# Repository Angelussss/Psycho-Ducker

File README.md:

# Psycho Ducker

Welcome to the Psycho Ducker, a 75% exploded keyboard project! This is a hot-swappable, compact, and efficient keyboard. Below, you'll find all the details you need to build and understand this project.

## Layout

The keyboard features a 75% exploded layout, offering a balance between functionality and compactness. The exploded design separates key clusters for a modern aesthetic and improved usability.

## Components

### Essentials

-   **MCU:** STM32F072CBT6.
    
-   **Switches:** Cherry MX style (supports both 3-pin and 5-pin switches).
    
-   **Keycaps:** Standard keycap set compatible with the Cherry MX stem.
    
-   **Diodes:** SOD-123.
    
-   **Hot-swap sockets:** Kailh are recommended.

### Optionals

-   **M2 screws** (to secure the PCB to the case or standoffs).
    
-   **M2 standoffs** (for added stability between the PCB and case).
    
-   **Stabilizers** (PCB-mounted, required for larger keys like the spacebar, enter, and shift).

## Required Tools

-   **Soldering iron**: Required for soldering pretty much the whole project.

- **heatgun**: Heavily hinted for soldering the micro. with a basic soldering iron is very hard.
    
-   **USB cable**: Required for connecting the keyboard to your computer. The PCB uses a usb type-C connector. Be sure to have at least one usable!

## Assembly Requirements

To assemble this keyboard, you'll need medium tin soldering skills, particularly for the micro.

## Notes

-   This keyboard's PCB is designed for hot-swapping switches, making possible to change the switches without de-soldering and re-soldering.
    
-   Firmware is powered by [QMK](https://qmk.fm/), a powerful and customizable open-source keyboard firmware.
    
-   This design has been tested thoroughly and functions reliably. However, as with any DIY project, minor adjustments may be needed based on your specific components.
    
-   Feel free to use this design for personal projects, but please do not edit or misuse it.
    
-in this design there are several types of cases you might wanna use. you can find the different materials and files in the "case" folder. The case is not necessary and is hands down the hardest part as it uses specific and expensive machinery, 

## Photos

-   **Finished Build:** ![fnished keyboard photo]
    
-   **Render:** ![pcb render] (https://github.com/Angelussss/Psycho-Ducker/blob/main/images/pcb_render.png)

## Contact

For any questions, feedback, or assistance, feel free to reach out via Telegram: @AngelusPSPS.

Thank you for exploring this project! Happy building and typing!

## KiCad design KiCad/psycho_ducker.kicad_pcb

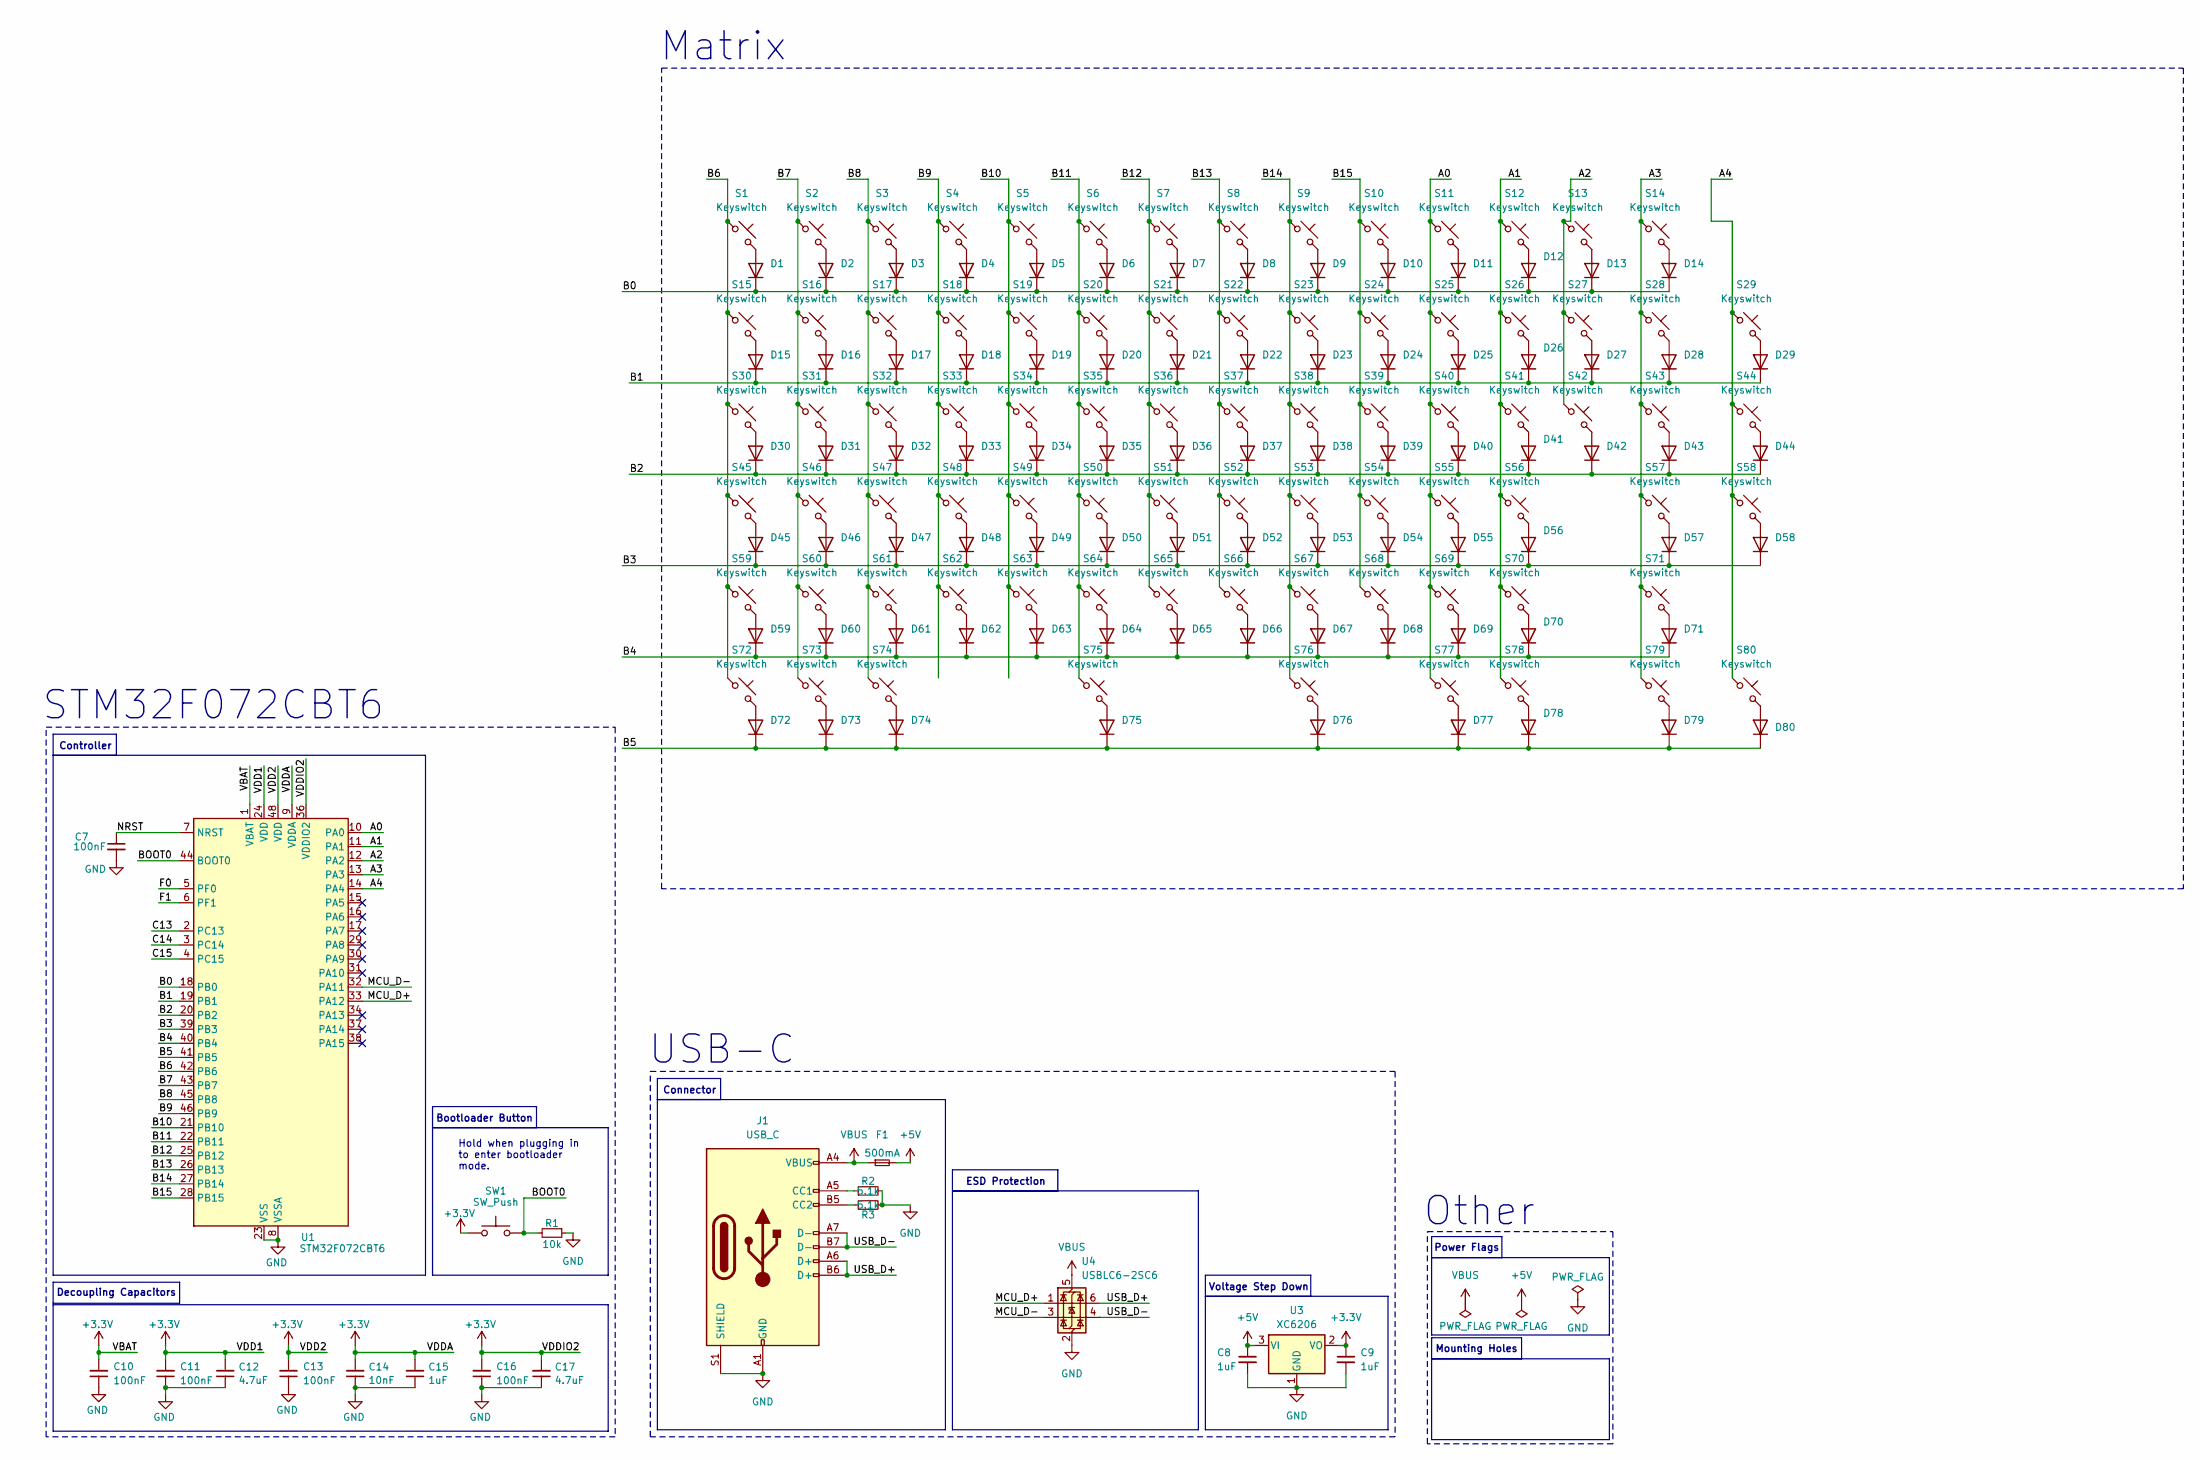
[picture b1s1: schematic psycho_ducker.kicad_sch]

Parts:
C7: 100nF; Capacitor_0402; LCSC C307331
C8, C9: 1uF; Capacitor_0402; LCSC C52923
C10, C11, C13, C16: 100nF; Capacitor_0402; MPN CL05B104KB54PNC; LCSC C307331
C12, C17: 4.7uF; Capacitor_0402; MPN CL05A475MP5NRNC; LCSC C23733
C14: 10nF; Capacitor_0402; MPN CL05B103KB5NNNC; LCSC C15195
C15: 1uF; Capacitor_0402; MPN CL05A105KA5NQNC; LCSC C52923
D1, D2, D3, D4, D5, D6, D7, D8, D9, D10, D11, D12, D13, D14, D15, D16, D17, D18, D19, D20, D21, D22, D23, D24, D25, D26, D27, D28, D29, D30, D31, D32, D33, D34, D35, D36, D37, D38, D39, D40, D41, D42, D43, D44, D45, D46, D47, D48, D49, D50, D51, D52, D53, D54, D55, D56, D57, D58, D59, D60, D61, D62, D63, D64, D65, D66, D67, D68, D69, D70, D71, D72, D73, D74, D75, D76, D77, D78, D79, D80: Diode; Diode_SOD-123
F1: 500mA; Fuse_0603; LCSC C210357
J1: USB_C; USB_C_HRO_TYPE-C-31-M-12; LCSC C165948
R1: 10k; R_0402_1005Metric; LCSC C25744
R2, R3: 5.1k; R_0402_1005Metric; LCSC C25905
S1, S2, S3, S4, S5, S6, S7, S8, S9, S10, S11, S12, S13, S14, S15, S16, S17, S18, S19, S20, S21, S22, S23, S24, S25, S26, S27, S29, S31, S32, S33, S34, S35, S36, S37, S38, S39, S40, S41, S42, S44, S46, S47, S48, S49, S50, S51, S52, S53, S54, S55, S56, S58, S60, S61, S62, S63, S64, S65, S66, S67, S68, S69, S71, S78, S79, S80: Keyswitch; Hotswap_MX_1.00u
S28: Keyswitch; Hotswap_MX_2.00u
S30, S43, S76, S77: Keyswitch; Hotswap_MX_1.50u
S45, S70: Keyswitch; Hotswap_MX_1.75u
S57, S59: Keyswitch; Hotswap_MX_2.25u
S72, S73, S74: Keyswitch; Hotswap_MX_1.25u
S75: Keyswitch; Hotswap_MX_6.25u
SW1: SW_Push; Button_TL3342; LCSC C115351
U1: STM32F072CBT6; Package_LQFP-48_7x7mm_P0.5; LCSC C81720
U3: XC6206; Voltage_SOT-23; LCSC C5446
U4: USBLC6-2SC6; ESD_SOT-23-6; LCSC C2827654

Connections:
+3.3V: C9.1, C10.2, C11.2, C12.2, C13.2, C14.2, C15.2, C16.2, C17.2, SW1.1, U1.1 (VBAT), U1.9 (VDDA), U1.24 (VDD), U1.36 (VDDIO2), U1.48 (VDD), U3.2 (VO)
+5V: C8.1, F1.2, U3.3 (VI)
/A0: S11.1, S25.1, S40.1, S55.1, S69.1, S77.1, U1.10 (PA0)
/A1: S12.1, S26.1, S41.1, S56.1, S70.1, S78.1, U1.11 (PA1)
/A2: S13.1, S27.1, S42.1, U1.12 (PA2)
/A3: S14.1, S28.1, S43.1, S57.1, S71.1, S79.1, U1.13 (PA3)
/A4: S29.1, S44.1, S58.1, S80.1, U1.14 (PA4)
/A5: U1.15 (PA5)
/A6: U1.16 (PA6)
/A7: U1.17 (PA7)
/A8: U1.29 (PA8)
/A9: U1.30 (PA9)
/A10: U1.31 (PA10)
/A13: U1.34 (PA13)
/A14: U1.37 (PA14)
/A15: U1.38 (PA15)
/B0: D1.1 (K), D2.1 (K), D3.1 (K), D4.1 (K), D5.1 (K), D6.1 (K), D7.1 (K), D8.1 (K), D9.1 (K), D10.1 (K), D11.1 (K), D12.1 (K), D13.1 (K), D14.1 (K), U1.18 (PB0)
/B1: D15.1 (K), D16.1 (K), D17.1 (K), D18.1 (K), D19.1 (K), D20.1 (K), D21.1 (K), D22.1 (K), D23.1 (K), D24.1 (K), D25.1 (K), D26.1 (K), D27.1 (K), D28.1 (K), D29.1 (K), U1.19 (PB1)
/B2: D30.1 (K), D31.1 (K), D32.1 (K), D33.1 (K), D34.1 (K), D35.1 (K), D36.1 (K), D37.1 (K), D38.1 (K), D39.1 (K), D40.1 (K), D41.1 (K), D42.1 (K), D43.1 (K), D44.1 (K), U1.20 (PB2)
/B3: D45.1 (K), D46.1 (K), D47.1 (K), D48.1 (K), D49.1 (K), D50.1 (K), D51.1 (K), D52.1 (K), D53.1 (K), D54.1 (K), D55.1 (K), D56.1 (K), D57.1 (K), D58.1 (K), U1.39 (PB3)
/B4: D59.1 (K), D60.1 (K), D61.1 (K), D62.1 (K), D63.1 (K), D64.1 (K), D65.1 (K), D66.1 (K), D67.1 (K), D68.1 (K), D69.1 (K), D70.1 (K), D71.1 (K), U1.40 (PB4)
/B5: D72.1 (K), D73.1 (K), D74.1 (K), D75.1 (K), D76.1 (K), D77.1 (K), D78.1 (K), D79.1 (K), D80.1 (K), U1.41 (PB5)
/B6: S1.1, S15.1, S30.1, S45.1, S59.1, S72.1, U1.42 (PB6)
/B7: S2.1, S16.1, S31.1, S46.1, S60.1, S73.1, U1.43 (PB7)
/B8: S3.1, S17.1, S32.1, S47.1, S61.1, S74.1, U1.45 (PB8)
/B9: S4.1, S18.1, S33.1, S48.1, S62.1, U1.46 (PB9)
/B10: S5.1, S19.1, S34.1, S49.1, S63.1, U1.21 (PB10)
/B11: S6.1, S20.1, S35.1, S50.1, S64.1, S75.1, U1.22 (PB11)
/B12: S7.1, S21.1, S36.1, S51.1, S65.1, U1.25 (PB12)
/B13: S8.1, S22.1, S37.1, S52.1, S66.1, U1.26 (PB13)
/B14: S9.1, S23.1, S38.1, S53.1, S67.1, S76.1, U1.27 (PB14)
/B15: S10.1, S24.1, S39.1, S54.1, S68.1, U1.28 (PB15)
/BOOT0: R1.2, SW1.2, U1.44 (BOOT0)
/C13: U1.2 (PC13)
/C14: U1.3 (PC14)
/C15: U1.4 (PC15)
/F0: U1.5 (PF0)
/F1: U1.6 (PF1)
/MCU_D+: U1.33 (PA12), U4.1 (I/O1)
/MCU_D-: U1.32 (PA11), U4.3 (I/O2)
/NRST: C7.1, U1.7 (NRST)
/USB_D+: J1.A6 (D+), J1.B6 (D+), U4.6 (I/O1)
/USB_D-: J1.A7 (D-), J1.B7 (D-), U4.4 (I/O2)
GND: C7.2, C8.2, C9.2, C10.1, C11.1, C12.1, C13.1, C14.1, C15.1, C16.1, C17.1, J1.A1 (GND), J1.A12 (GND), J1.B1 (GND), J1.B12 (GND), J1.S1 (SHIELD), R1.1, R2.2, R3.2, U1.8 (VSSA), U1.23 (VSS), U1.35 (VSS), U1.47 (VSS), U3.1 (GND), U4.2 (GND)
unnamed: D1.2 (A), S1.2
unnamed: D2.2 (A), S2.2
unnamed: D3.2 (A), S3.2
unnamed: D4.2 (A), S4.2
unnamed: D5.2 (A), S5.2
unnamed: D6.2 (A), S6.2
unnamed: D7.2 (A), S7.2
unnamed: D8.2 (A), S8.2
unnamed: D9.2 (A), S9.2
unnamed: D10.2 (A), S10.2
unnamed: D11.2 (A), S11.2
unnamed: D12.2 (A), S12.2
unnamed: D13.2 (A), S13.2
unnamed: D14.2 (A), S14.2
unnamed: D15.2 (A), S15.2
unnamed: D16.2 (A), S16.2
unnamed: D17.2 (A), S17.2
unnamed: D18.2 (A), S18.2
unnamed: D19.2 (A), S19.2
unnamed: D20.2 (A), S20.2
unnamed: D21.2 (A), S21.2
unnamed: D22.2 (A), S22.2
unnamed: D23.2 (A), S23.2
unnamed: D24.2 (A), S24.2
unnamed: D25.2 (A), S25.2
unnamed: D26.2 (A), S26.2
unnamed: D27.2 (A), S27.2
unnamed: D28.2 (A), S28.2
unnamed: D29.2 (A), S29.2
unnamed: D30.2 (A), S30.2
unnamed: D31.2 (A), S31.2
unnamed: D32.2 (A), S32.2
unnamed: D33.2 (A), S33.2
unnamed: D34.2 (A), S34.2
unnamed: D35.2 (A), S35.2
unnamed: D36.2 (A), S36.2
unnamed: D37.2 (A), S37.2
unnamed: D38.2 (A), S38.2
unnamed: D39.2 (A), S39.2
unnamed: D40.2 (A), S40.2
unnamed: D41.2 (A), S41.2
unnamed: D42.2 (A), S42.2
unnamed: D43.2 (A), S43.2
unnamed: D44.2 (A), S44.2
unnamed: D45.2 (A), S45.2
unnamed: D46.2 (A), S46.2
unnamed: D47.2 (A), S47.2
unnamed: D48.2 (A), S48.2
unnamed: D49.2 (A), S49.2
unnamed: D50.2 (A), S50.2
unnamed: D51.2 (A), S51.2
unnamed: D52.2 (A), S52.2
unnamed: D53.2 (A), S53.2
unnamed: D54.2 (A), S54.2
unnamed: D55.2 (A), S55.2
unnamed: D56.2 (A), S56.2
unnamed: D57.2 (A), S57.2
unnamed: D58.2 (A), S58.2
unnamed: D59.2 (A), S59.2
unnamed: D60.2 (A), S60.2
unnamed: D61.2 (A), S61.2
unnamed: D62.2 (A), S62.2
unnamed: D63.2 (A), S63.2
unnamed: D64.2 (A), S64.2
unnamed: D65.2 (A), S65.2
unnamed: D66.2 (A), S66.2
unnamed: D67.2 (A), S67.2
unnamed: D68.2 (A), S68.2
unnamed: D69.2 (A), S69.2
unnamed: D70.2 (A), S70.2
unnamed: D71.2 (A), S71.2
unnamed: D72.2 (A), S72.2
unnamed: D73.2 (A), S73.2
unnamed: D74.2 (A), S74.2
unnamed: D75.2 (A), S75.2
unnamed: D76.2 (A), S76.2
unnamed: D77.2 (A), S77.2
unnamed: D78.2 (A), S78.2
unnamed: D79.2 (A), S79.2
unnamed: D80.2 (A), S80.2
unnamed: J1.A5 (CC1), R2.1
unnamed: J1.B5 (CC2), R3.1
VBUS: F1.1, J1.A4 (VBUS), J1.A9 (VBUS), J1.B4 (VBUS), J1.B9 (VBUS), U4.5 (VBUS)

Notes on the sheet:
Hold when plugging in to enter bootloader mode.
STM32F072CBT6
USB-C
Mounting Holes
Decoupling Capacitors
Controller
ESD Protection
Power Flags
Voltage Step Down
Other
Bootloader Button
Matrix
Connector

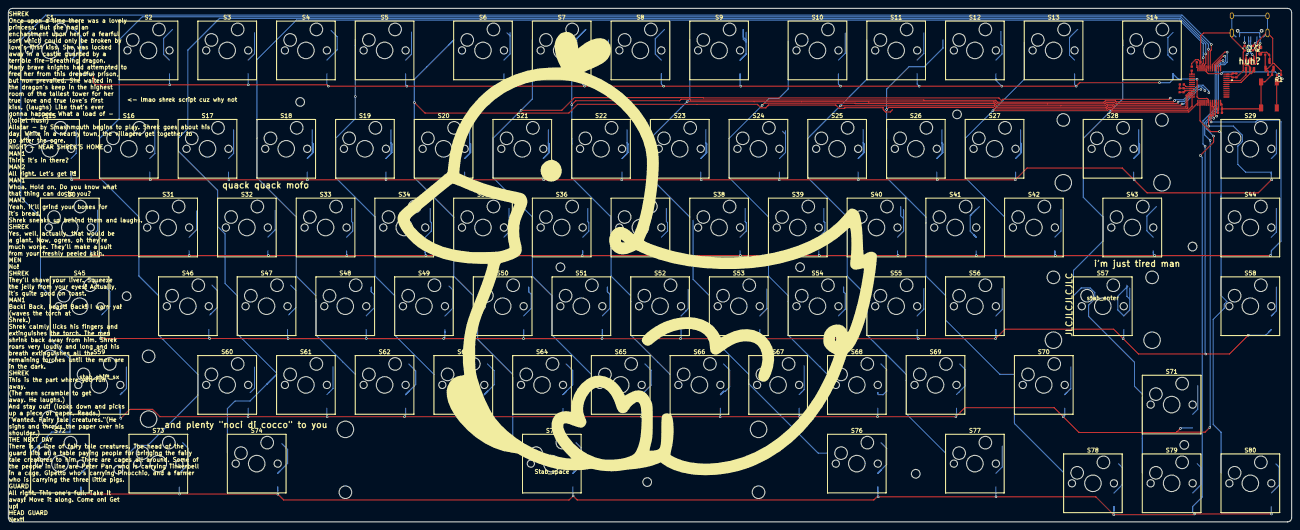
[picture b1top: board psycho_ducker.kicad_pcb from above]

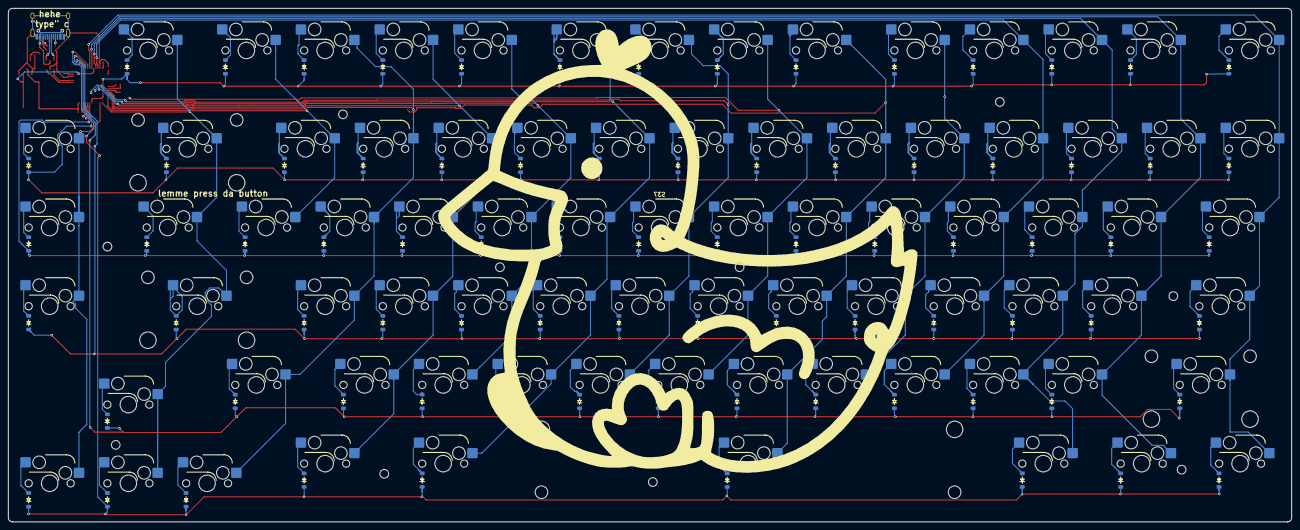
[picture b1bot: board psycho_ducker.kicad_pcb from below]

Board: 2 copper layers, 310.6 x 124.3 mm, 186 parts (82 on the bottom side), 113 nets.

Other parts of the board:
Stab_space: Stabilizer_MX_6.25u
backduck: LOGO
frontduck: LOGO
stab_backspace: Stabilizer_MX_2.00u
stab_enter: Stabilizer_MX_2.00u
stab_shift_sx: Stabilizer_MX_2.00u

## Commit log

2024-12-16 added layout from KLE
2024-12-16 edited README
2025-02-24 added v1.0.0 gerber files
2025-03-21 feat: added pcb render
2025-03-21 feat: added keyboard cads
2025-03-21 feat: added JLC order number code into f_silkscreen
2025-03-21 feat: updated production folder
2025-04-11 feat: added interactive bom
2025-04-11 feat: added pdf plot
2025-04-11 fix: c7 footprint, jlc code repetition, shrek typo and added duck
2025-04-11 feat: added micro orientation reference
2025-05-13 feat: added firmware.bin
2025-08-13 feat: added layout.json
2025-08-13 feat: started pcb front plate case
2025-08-14 fix: removed useless files
2025-08-14 feat: added front plate dxf base file
2025-08-15 feat: added front plate pcb
2025-08-15 feat: added backplate
2025-08-15 fix: useless files
2025-08-15 fix: backplate filling
2025-08-16 feat: backplate now has mounting holes compatible with the main pcb
2025-08-17 feat: changed backplate pattern
2025-08-17 feat: added rubber feet placement
2025-08-17 fix: removed sch file as it is useless
2025-08-17 feat: added _style_ to the pcb
2025-08-17 feat: added Bo Burnham cit
2025-08-17 feat: added JLC PCB required text
2025-08-17 feat: added rounded corners
2025-08-17 feat: added mounting holes
2025-08-18 fix: minor fixes
2025-08-18 fix: removed useless folder
2025-08-18 feat: added latest production file
2025-08-18 fix: moved backplate folder content into the backplate folder before said backplate folder, making the backplate folder unique and not a redundant backplate folder just like the backplate folder prio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
2025-08-19 fix: removed useless file
2025-08-21 fix: renamed folders
2025-08-26 fix: file placement
2025-09-24 fix: updated differential usb line
2025-09-28 fix: removed MCU and various IC for a start=over routing journey
2025-09-28 fix: removed holes from schematic
2025-09-29 fix: disconnected unused pins
2025-09-29 feat: updated routing
2025-09-29 feat: added 3V3 and GND planes
2026-01-26 feat: added WS2812B to the pcb
2026-01-26 fix: mounting holes placement
2026-01-26 fix: final fixes
2026-03-06 fix: added border for plate mount
2026-04-28 feat: source firmware code is now aviable
